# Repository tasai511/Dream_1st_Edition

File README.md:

# ドリーム1号 素振り記録アプリ

素振り練習用デバイス「ドリーム1号」の記録用PWAです。HTML / CSS / JavaScriptのみで構成され、アプリ本体は `app/` フォルダに入っています。

## できること

- 名前とバットを複数登録
- 日付、名前、バット、素振り回数、平均スコア、ベストスコアを記録
- 同じ日付・名前・バットの記録は自動で合算
- 平均スコアは回数による加重平均で計算
- ベストスコアは最大値を採用
- 最近の入力履歴から編集・削除
- 期間、名前、バットで絞り込んだグラフ表示
- CSVエクスポート / インポート
- オフライン動作

## GitHub Pagesで公開する方法

1. このリポジトリをGitHubへpushします。
2. GitHubのリポジトリ画面で `Settings` を開きます。
3. `Pages` を開きます。
4. `Build and deployment` の `Source` で `Deploy from a branch` を選びます。
5. `Branch` で公開したいブランチと `/root` を選び、保存します。
6. 表示されたURLを開くと、自動で `app/` のアプリが開きます。

アプリを直接開く場合は、GitHub PagesのURL末尾に `/app/` を付けてください。

## PWAとしてホーム画面に追加する方法

### iPhone / iPad

1. SafariでGitHub PagesのURLを開きます。
2. 共有ボタンを押します。
3. `ホーム画面に追加` を選びます。
4. 名前を確認して追加します。

### Android

1. ChromeでGitHub PagesのURLを開きます。
2. メニューから `ホーム画面に追加` または `アプリをインストール` を選びます。
3. 確認して追加します。

## CSVエクスポート / インポート

### エクスポート

`CSVエクスポート` ボタンを押すと、全記録をCSVファイルとして保存します。CSVには以下の列が含まれます。

- 名前
- バット
- 日付
- 回数
- 平均
- ベスト

### インポート

`CSVインポート` からCSVファイルを選ぶと、記録を復元できます。既存データと同じ日付・名前・バットの行は合算されます。不正な行はスキップされ、読み込み後にスキップ件数が表示されます。

## データ保存について

データはすべて端末ローカルのIndexedDBに保存されます。サーバー保存、ログイン、クラウド同期はありません。

端末を変更する場合やブラウザのデータを消す場合は、事前にCSVエクスポートでバックアップしてください。新しい端末ではCSVインポートで移行できます。

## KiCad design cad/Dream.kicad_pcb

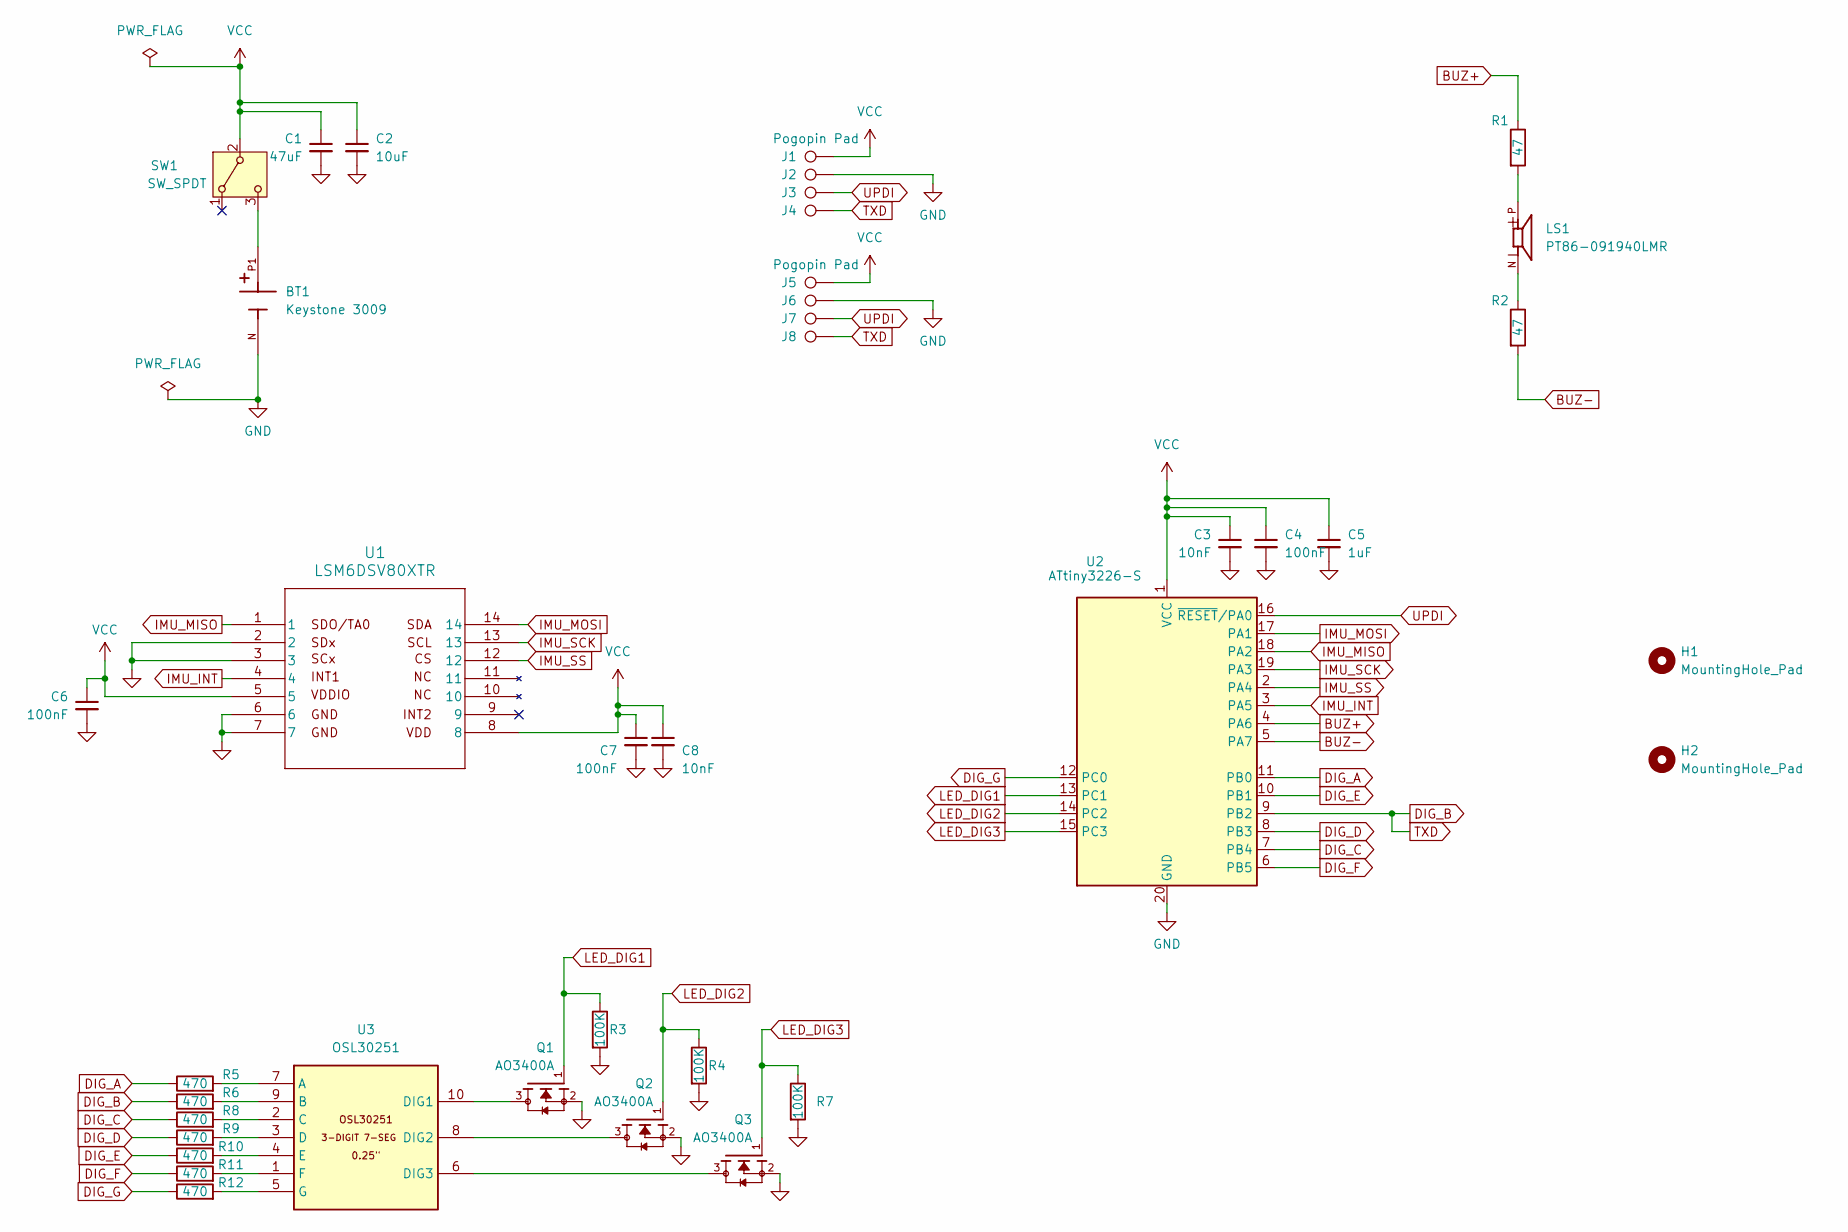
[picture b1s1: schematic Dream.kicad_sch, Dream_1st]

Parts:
BT1: Keystone 3009; BAT_3009; PARTREV G; DigiKey_Part_Number 36-1052CT-ND
C1: 47uF; C_1210_3225Metric_Pad1.33x2.70mm_HandSolder
C2: 10uF; C_0603_1608Metric_Pad1.08x0.95mm_HandSolder
C3, C8: 10nF; C_0603_1608Metric_Pad1.08x0.95mm_HandSolder
C4, C6, C7: 100nF; C_0603_1608Metric_Pad1.08x0.95mm_HandSolder
C5: 1uF; C_0603_1608Metric_Pad1.08x0.95mm_HandSolder
H1, H2: MountingHole_Pad; MountingHole_2.2mm_M2_Pad_TopOnly
J1, J2, J3, J4, J5, J6, J7, J8: Pogopin Pad; TestPoint_Pad_D1.5mm
LS1: PT86-091940LMR; Buzzer_PT86-091940LMR; PARTREV December 26, 2017; DigiKey_Part_Number 490-4698-1-ND
Q1, Q2, Q3: AO3400A; SOT95P280X125-3N; PARTREV L; DigiKey_Part_Number 785-1000-1-ND
R1, R2: 47; R_0603_1608Metric_Pad0.98x0.95mm_HandSolder
R3, R4, R7: 100K; R_0603_1608Metric_Pad0.98x0.95mm_HandSolder
R5, R6, R8, R9, R10, R11, R12: 470; R_0603_1608Metric_Pad0.98x0.95mm_HandSolder
SW1: SW_SPDT; MSS22D18
U1: LSM6DSV80XTR; QFN_LSM6DSV80XTR_STM
U2: ATtiny3226-S; SOIC-20W_7.5x12.8mm_P1.27mm
U3: OSL30251

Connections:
BUZ+: R1.1, U2.4 (PA6)
BUZ-: R2.2, U2.5 (PA7)
DIG_A: R5.1, U2.11 (PB0)
DIG_B: J4.1 (1_1), J8.1 (1_1), R6.1, U2.9 (PB2)
DIG_C: R8.1, U2.7 (PB4)
DIG_D: R9.1, U2.8 (PB3)
DIG_E: R10.1, U2.10 (PB1)
DIG_F: R11.1, U2.6 (PB5)
DIG_G: R12.1, U2.12 (PC0)
GND: BT1.N, C1.2, C2.2, C3.2, C4.2, C5.2, C6.2, C7.2, C8.2, J2.1 (1_1), J6.1 (1_1), Q1.2, Q2.2, Q3.2, R3.2, R4.2, R7.2, U1.2, U1.3, U1.6, U1.7, U2.20 (GND)
IMU_INT: U1.4, U2.3 (PA5)
IMU_MISO: U1.1, U2.18 (PA2)
IMU_MOSI: U1.14, U2.17 (PA1)
IMU_SCK: U1.13, U2.19 (PA3)
IMU_SS: U1.12, U2.2 (PA4)
LED_DIG1: Q1.1, R3.1, U2.13 (PC1)
LED_DIG2: Q2.1, R4.1, U2.14 (PC2)
LED_DIG3: Q3.1, R7.1, U2.15 (PC3)
unnamed: LS1.N, R2.1
unnamed: LS1.P, R1.2
unnamed: BT1.P1, BT1.P2, SW1.3 (C)
unnamed: R5.2, U3.7 (A)
unnamed: R6.2, U3.9 (B)
unnamed: R8.2, U3.2 (C)
unnamed: R9.2, U3.3 (D)
unnamed: Q1.3, U3.10 (DIG1)
unnamed: Q2.3, U3.8 (DIG2)
unnamed: Q3.3, U3.6 (DIG3)
unnamed: R10.2, U3.4 (E)
unnamed: R11.2, U3.1 (F)
unnamed: R12.2, U3.5 (G)
UPDI: J3.1 (1_1), J7.1 (1_1), U2.16 (~RESET/PA0)
VCC: C1.1, C2.1, C3.1, C4.1, C5.1, C6.1, C7.1, C8.1, J1.1 (1_1), J5.1 (1_1), SW1.2 (B), U1.5, U1.8, U2.1 (VCC)

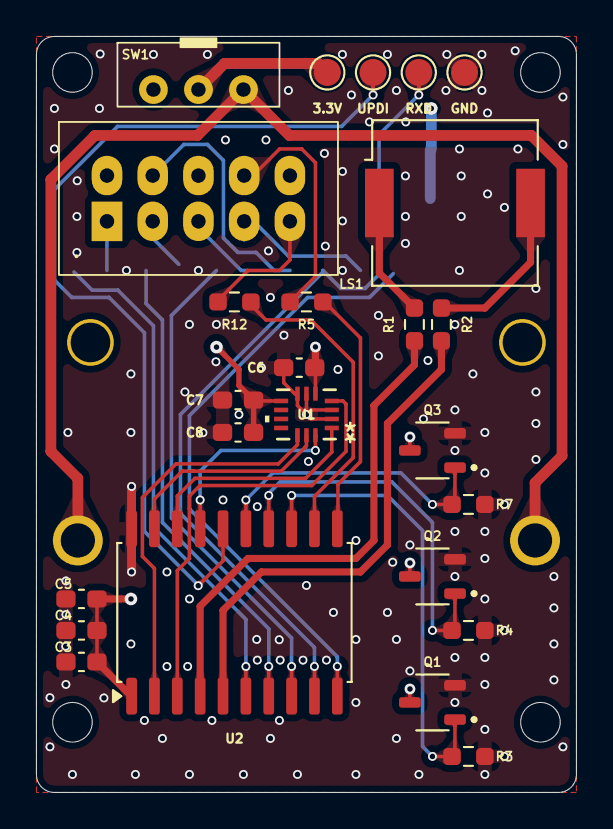
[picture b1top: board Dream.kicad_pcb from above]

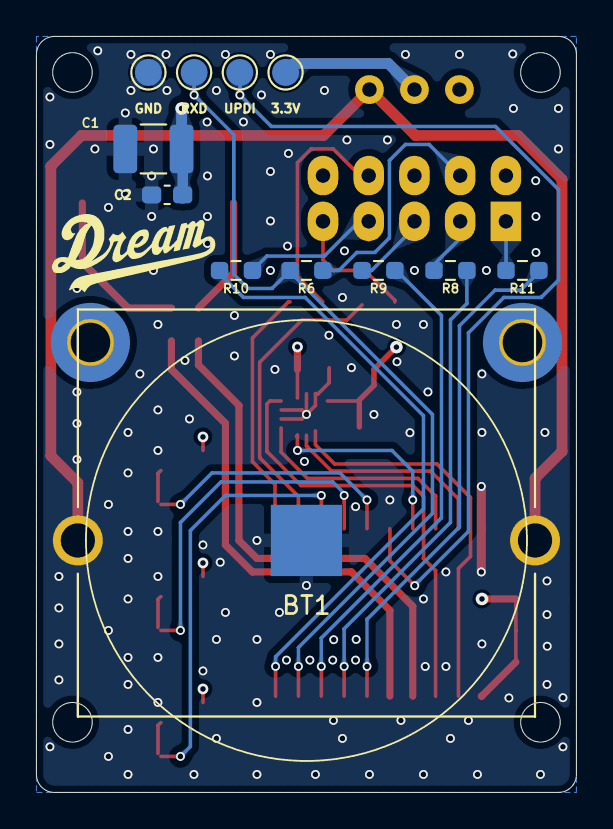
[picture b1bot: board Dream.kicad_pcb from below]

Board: 4 copper layers, 30.0 x 42.0 mm, 39 parts (14 on the bottom side), 33 nets.

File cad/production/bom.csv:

Designator,Footprint,Quantity,Value,LCSC Part #
BT1,BAT_3009,1,Keystone 3009,
C1,1210,1,47uF,
C2,0603,1,10uF,
"C3, C8",0603,2,10nF,
"C4, C6, C7",0603,3,100nF,
C5,0603,1,1uF,
"J1, J2, J3, J4, J5, J6, J7, J8",TestPoint_Pad_D1.5mm,8,Pogopin Pad,
LS1,Buzzer_PT86-091940LMR,1,PT86-091940LMR,
"Q1, Q2, Q3",SOT95P280X125-3N,3,AO3400A,
"R1, R2",0603,2,47,
"R10, R11, R12, R5, R6, R8, R9",0603,7,470,
"R3, R4, R7",0603,3,100K,
SW1,MSS22D18,1,SW_SPDT,
U1,QFN_LSM6DSV80XTR_STM,1,LSM6DSV80XTR,
U2,SOIC-20W_7.5x12.8mm_P1.27mm,1,ATtiny3226-S,
U3,OSL30251,1,OSL30251,

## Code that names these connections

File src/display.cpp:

#include "display.h"

namespace {

const uint8_t kSegmentPins[] = {
    PIN_PB0,  // A
    PIN_PB2,  // B
    PIN_PB4,  // C
    PIN_PB3,  // D
    PIN_PB1,  // E
    PIN_PB5,  // F
    PIN_PC0,  // G
};

const uint8_t kDigitPins[] = {
    PIN_PC1,
    PIN_PC2,
    PIN_PC3,
};

const uint8_t kDigitCount = 3;
const uint16_t kMaxDisplayValue = 999;
const uint16_t kMultiplexIntervalMs = 2;

// Bit order is A B C D E F G. Common cathode: segment HIGH lights segment.
const uint8_t kSegmentsForDigit[] = {
    0b1111110,  // 0
    0b0110000,  // 1
    0b1101101,  // 2
    0b1111001,  // 3
    0b0110011,  // 4
    0b1011011,  // 5
    0b1011111,  // 6
    0b1110000,  // 7
    0b1111111,  // 8
    0b1111011,  // 9
};

uint8_t digits[kDigitCount] = {0, 0, 0};
bool blankDigit[kDigitCount] = {true, true, true};
uint8_t activeDigit = 0;
uint32_t visibleUntilMs = 0;
uint32_t lastMultiplexMs = 0;

void disableDigits() {
  for (uint8_t i = 0; i < kDigitCount; ++i) {
    digitalWrite(kDigitPins[i], LOW);
  }
}

void clearSegments() {
  for (uint8_t i = 0; i < sizeof(kSegmentPins); ++i) {
    digitalWrite(kSegmentPins[i], LOW);
  }
}

void setSegments(uint8_t value) {
  if (value > 9) {
    clearSegments();
    return;
  }

  const uint8_t mask = kSegmentsForDigit[value];
  for (uint8_t i = 0; i < sizeof(kSegmentPins); ++i) {
    const uint8_t bit = 6 - i;
    digitalWrite(kSegmentPins[i], (mask & (1 << bit)) ? HIGH : LOW);
  }
}

void prepareDigits(uint16_t value) {
  if (value > kMaxDisplayValue) {
    value = kMaxDisplayValue;
  }

  digits[0] = value / 100;
  digits[1] = (value / 10) % 10;
  digits[2] = value % 10;

  blankDigit[0] = value < 100;
  blankDigit[1] = value < 10;
  blankDigit[2] = false;
}

}  // namespace

namespace Display {

void begin() {
  for (uint8_t i = 0; i < sizeof(kSegmentPins); ++i) {
    pinMode(kSegmentPins[i], OUTPUT);
  }
  for (uint8_t i = 0; i < kDigitCount; ++i) {
    pinMode(kDigitPins[i], OUTPUT);
  }

  off();
}

void showNumber(uint16_t value, uint32_t nowMs, uint16_t durationMs) {
  prepareDigits(value);
  visibleUntilMs = nowMs + durationMs;
  lastMultiplexMs = 0;
}

void update(uint32_t nowMs) {
  if (!isOn(nowMs)) {
    off();
    return;
  }

  if (lastMultiplexMs != 0 && nowMs - lastMultiplexMs < kMultiplexIntervalMs) {
    return;
  }
  lastMultiplexMs = nowMs;

  disableDigits();
  clearSegments();

  activeDigit = (activeDigit + 1) % kDigitCount;
  if (!blankDigit[activeDigit]) {
    setSegments(digits[activeDigit]);
    digitalWrite(kDigitPins[activeDigit], HIGH);
  }
}

void off() {
  visibleUntilMs = 0;
  disableDigits();
  clearSegments();
}

bool isOn(uint32_t nowMs) {
  return visibleUntilMs != 0 && static_cast<int32_t>(visibleUntilMs - nowMs) > 0;
}

}  // namespace Display

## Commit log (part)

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2026-04-23 Add initial project configuration and documentation files
    - Create .gitignore to exclude build artifacts and IDE settings
    - Add .vscode/extensions.json for recommended extensions
    - Include README files for header files, libraries, and tests
    - Set up platformio.ini for ATtiny3226 configuration
    - Implement main.cpp for basic LED blinking functionality
2026-04-23 Remove backup files and update .gitignore to exclude Dream-backups directory
2026-04-24 Add dream firmware files.
2026-04-24 Add Dream firmware files
2026-04-24 delete
2026-04-26 acc 16g to 64g
2026-04-26 sync
2026-04-26 ignore
2026-04-28 golden1
2026-04-29 good
2026-04-30 Add milestone swing completion beep
2026-04-30 Use continuous swing capture without tap UI
2026-05-01 Finalize Dream-1 candidate firmware
2026-05-01 Finalize polling sleep behavior
2026-05-02 Final Candidate (Polling)
2026-05-02 Tap Polling
2026-05-02 Finalize tap polling with idle sleep
2026-05-02 Final Candidate
2026-05-04 ad strengthScore
2026-05-05 Small Tuning
2026-05-05 edit context.md
2026-05-10 new score algo
2026-05-10 add app
2026-05-11 small edit
2026-05-11 React app
2026-05-11 Add GitHub Pages deployment workflow
2026-05-11 Improve mobile swing log dashboard
2026-05-11 Rename home filter section
2026-05-11 Remove home filter heading
2026-05-11 Modernize bat selector styling
2026-05-11 Refine bat selector sizing and icons
2026-05-11 Tighten bat selector design
2026-05-11 Compact home filters
2026-05-11 Balance home filter columns
2026-05-11 Stack home filters vertically
2026-05-11 Remove chart axis frame
2026-05-11 Add touch zoom to score chart
2026-05-11 Use range as chart viewport
2026-05-11 Expand demo data to two years
2026-05-11 Fix chart zoom and hover targeting
2026-05-11 Simplify chart range presets
2026-05-11 Polish swing log mobile experience
2026-05-11 Polish mobile swing dashboard
2026-05-11 Refine swing entry defaults
2026-05-11 Switch to accent color themes
2026-05-11 Improve landscape layout and swing art
2026-05-11 Polish chart tooltip and controls
2026-05-11 Group badges by category
2026-05-11 Refine swing input and badge indicators
2026-05-11 Move tabs and refresh branding
2026-05-11 Polish header badges and chart hover
2026-05-11 Update brand title and swing art
2026-05-11 Enhance swing art glow
2026-05-11 Refine app title lockup
2026-05-11 Update app icon artwork
2026-05-11 Adjust app title typography
2026-05-11 Refine title and bat icon
2026-05-11 Improve landscape header and chart layout
2026-05-11 Use image asset for bat icon
2026-05-11 Fix comparison chart colors
2026-05-11 Refresh bat icon asset
2026-05-11 CSS change
2026-05-11 Update swing hero artwork
2026-05-11 Revert "Update swing hero artwork"
    This reverts commit ac197d8993e02cb9b4343f46764ec6726235269f.
2026-05-11 rollback
2026-05-12 Remove Dream logo from Swing Log UI
2026-05-12 Reorder home dashboard sections
2026-05-12 Nest home score sections
2026-05-12 Move filters above score summary
2026-05-12 Revise home achievements and records
2026-05-12 Fix achievement meter text sizing
2026-05-12 Compact home bat selector
2026-05-12 Lighten bat selector text
2026-05-12 Refine achievement meter visuals
2026-05-12 Fix achievement meter arc rendering
2026-05-12 Size achievement meter SVG
2026-05-12 Hide incomplete meter track
2026-05-12 Limit meter glow to progress arc
2026-05-12 Enlarge and stabilize achievement meter
2026-05-12 Fit total swing value beside meter
2026-05-12 Reduce meter badge reserve space
2026-05-12 Align achievement meter centers
2026-05-12 Float meter badges beside right aligned arcs
2026-05-12 Place meter badges in top right grid
2026-05-12 Offset meters away from badge grid
2026-05-12 Shift achievement meters further left
2026-05-12 Right align total meter with score meters
2026-05-12 Center align meters and slim arcs
2026-05-12 Use layered arcs for mobile meter glow
2026-05-12 Soften mobile meter glow
2026-05-12 Align meter glow layer caps
2026-05-12 Match score meter glow strength
2026-05-12 Move meter badges to left corner
2026-05-12 Nudge meter badges right
2026-05-12 Reorder meter badge grid
2026-05-12 Show all time score badges and align meters
2026-05-12 Replace meter badges with goal badge
2026-05-12 Use theme color for record charts
2026-05-12 Restore best score line color
2026-05-12 Revise periods badges and home summaries
2026-05-12 Refine charts, badges, and theme controls
2026-05-12 Fix mobile bar chart rendering
2026-05-12 Restore chart styling and add y-axis
2026-05-12 Strengthen chart y-axis visibility
2026-05-12 Add vertical chart grid lines
2026-05-12 Strengthen vertical grid lines
2026-05-12 Refresh earned badge layout
2026-05-12 Fix badge labels and layout
2026-05-12 Standardize badge chip styling
2026-05-12 Align badge chips across views
2026-05-12 Document badge and home UI spec
2026-05-12 Remove existing badge rules
2026-05-12 Add home repeatable badges
2026-05-12 Add cumulative home range
2026-05-12 Refine home period units
2026-05-12 Rework home period layout
2026-05-12 Fix home tabs and chart width
2026-05-12 Blend home tabs into card
2026-05-12 Tighten home tab labels
2026-05-12 Apply modern flat app styling
2026-05-12 Switch flat styling to dark mode
2026-05-12 Flatten home card details
2026-05-12 Simplify flat dark home styling
2026-05-12 Embed home range tabs in card
2026-05-12 Simplify home date range labels
2026-05-12 Refine flat dark app controls
2026-05-12 Tighten tabs and neutralize card borders
2026-05-12 Update home meters and badge targets
2026-05-12 Simplify home card hierarchy
2026-05-12 Polish meter badges and pending state
2026-05-12 Align home controls with flat tabs
2026-05-12 Blend history section and meter popovers
2026-05-12 Match history background to card
2026-05-12 Refine app badges and home layout
2026-05-12 Update badge meter labels
2026-05-12 Align badge meter details
2026-05-13 Refine badge progress meters
2026-05-13 Bundle app icon assets
2026-05-13 Position meter badge on ring endpoint
2026-05-13 Refine chart tooltip and CSV controls
2026-05-13 Tone down calendar edit button
2026-05-13 Add rarity tabs to badge collection
2026-05-13 Prototype version 2 home cards
2026-05-13 Refine home and cumulative cards
2026-05-13 Refine history and badge interactions
2026-05-13 Polish responsive mobile GUI
2026-05-13 Brush up home badge UI
2026-05-13 Refine daily badge presentation
2026-05-13 Allow demo data without registered names
2026-05-13 Fix Pages icon asset paths
2026-05-13 Refine score card badge labels
2026-05-13 Prevent badge popover click-through
2026-05-13 Restore chart pan and pinch data range
2026-05-13 Adjust score badge label and stamp
2026-05-13 Space score badge label from badge
2026-05-13 Improve GET stamp contrast
2026-05-13 Dismiss chart hover on outside tap
2026-05-13 Fix count bar chart scrolling
2026-05-13 Refine score chart points and tooltip
2026-05-14 Compact today record entry
2026-05-14 Square score card badges
2026-05-14 Refine today record entry trigger
2026-05-14 Flatten score badge label text
2026-05-14 Bundle rarity icons for Pages
2026-05-14 Refine home entry and badge styling
2026-05-14 Fix badge icons on Pages
2026-05-14 Render rarity icons inline
2026-05-14 Revert "Fix badge icons on Pages"
    This reverts commit 8385b9404d70a4897c3e9f659d611a69772bb4e4.
2026-05-14 Use PNG rarity badges on score cards
2026-05-14 Remove score badge frame
2026-05-14 Make PNG rarity badge backgrounds transparent
2026-05-14 Add glow to score badge images
2026-05-14 Normalize transparent badge PNGs
2026-05-14 Strengthen badge image glow
2026-05-14 Make score badge images glow
2026-05-14 Scale badge glow by rarity
2026-05-14 Tune rarity badge glow levels
2026-05-14 Normalize high rarity badge PNGs
2026-05-14 Match home badge preview styling
2026-05-14 Increase score badge label size
2026-05-14 Rename period count badges
2026-05-14 Nudge rarity labels upward
2026-05-14 Enlarge score badge counts
2026-05-14 Stabilize Pages badge rendering
2026-05-14 Hide badge point meter icons
2026-05-14 Use rarity badge gallery as tabs
2026-05-14 Flatten badge collection rarity section
2026-05-14 Simplify collection rarity heading
2026-05-14 Highlight collection rarity initial
2026-05-14 Remove score badge names
2026-05-14 Remove bat selection radios
2026-05-14 Animate score card progress on record
2026-05-14 Slow score progress animation
2026-05-14 Prefill low addition test score
2026-05-14 Refine home charts and navigation
2026-05-14 Refine chart and badge styling
2026-05-14 Adjust mobile chart width
2026-05-14 Relax mobile chart width
2026-05-14 Widen mobile chart area
2026-05-14 Slim bottom navigation
2026-05-14 Use straight chart lines
2026-05-14 Expand line chart plot upward
2026-05-15 チャレンジ画面の記録レイアウトを更新
2026-05-15 ホームと記録画面のUIを調整
2026-05-15 使ったバット見出しの位置を調整
2026-05-15 記録タブのスコアカード表示を調整
2026-05-15 チャレンジと記録のカード列数を調整
2026-05-15 Tune record UI and optimize badge images
2026-05-15 Refine challenge and data flows
2026-05-15 Tune input animation test flow
2026-05-15 Fix input button recovery state
2026-05-15 Leave today empty in demo data
2026-05-16 Refine settings registration UI
2026-05-16 Match home input OK button styling
2026-05-16 Save current swing log layout state
2026-05-16 Refine score card layout and badge states
2026-05-16 Add challenge range tabs and yearly badges
2026-05-16 Add today shortcut to home calendar
2026-05-16 Add background image assets
2026-05-16 Restore Pages deploy branch setting
2026-05-17 Restyle app with ballpark card UI
2026-05-17 Use rounded app font
2026-05-18 Refine card polish and tab styling
2026-05-18 Refine card layouts and tab behavior
2026-05-18 Fix Pages background rendering
2026-05-18 Refine score cards and fix Pages background
2026-05-18 Polish paper-style input card
2026-05-18 Polish paper card and score badges
2026-05-18 Polish swing log UI
2026-05-18 Tune background fade and labels
2026-05-19 Polish badge and bat card interactions
2026-05-19 Refine test data and tab styling
2026-05-19 Tune best card color and bottom nav height
2026-05-19 Refresh app icons
2026-05-19 Polish score bars and mobile UI
2026-05-19 Refine score bar badge fill
2026-05-20 Tune score bar animation styling
2026-05-21 Adjust badge reward alignment
2026-05-21 Move badge input underline closer
2026-05-21 Adjust badge points card layout
2026-05-21 Update badge collection and responsive UI polish
2026-05-21 Use pen asset for badge edit indicators
2026-05-21 Use SVG pen for badge edit indicators
2026-05-21 Update badge and record card UI
2026-05-22 Tune badge reward styling
2026-05-22 Update app icons
2026-05-24 Rebuild Dream Log badge system and assets
2026-05-24 S_silver_nameplate update
2026-05-24 update images
2026-05-25 Refine badge chip layout and icon styling
2026-05-25 Update cards
2026-05-25 Refine badge plates and UI styling
2026-05-25 Adjust milestone icon fill behavior
2026-05-25 Rework badge collection categories
2026-05-25 Restore badge collection nameplates
2026-05-27 Add yearly score challenge badges
2026-05-27 Restore badge card inner outline
2026-05-27 Add first-get badge showcase
2026-05-27 Add fixed UI sound effects
2026-05-27 Document badge list
2026-05-27 Cache audio effects for PWA
2026-05-27 Add startup splash animation
2026-05-28 Finalyze User Interface
2026-05-30 Simplify challenge and badge progression
2026-05-30 Refine challenge score progress UI
2026-05-30 Finalize badge and challenge UI
2026-05-30 Adjust input card labels
2026-05-30 Split score badge categories
2026-05-31 Update first milestone badge names
2026-05-31 Refine tablet display and orientation
2026-05-31 Stabilize fixed-width app layout
2026-05-31 Refine demo data and responsive scaling
2026-06-01 Stretch bottom nav background
2026-06-01 Fix bottom nav background layer
2026-06-01 Make bottom nav span viewport
2026-06-01 Bump app cache version
2026-06-01 Add user manual deck
2026-06-01 startup guide update
2026-06-02 Refine swing scoring telemetry
2026-06-04 Refine swing scoring window
2026-06-04 docs Update
2026-06-04 Wrap Christmas badge nameplate
2026-06-04 Add graph navigation controls
2026-06-04 Overwrite records on CSV import
2026-06-04 Fix bottom nav scaling on wide screens
2026-06-08 Set swing score weights to 500 each
2026-06-08 Update instruction documents
